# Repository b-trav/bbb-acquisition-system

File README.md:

# BEAGLEBONE BLACK ACQUISITION SYSTEM

__IMPORTANT: This project was last updated in 2017, so many commands and links are likely to be out of date.__

## Introduction

This project will show you how to create an 8 channel 24-bit 130 kSPS 
data acquisition system using a Beaglebone Black, four ADS1271 
Evaluation modules and a few other electronic bits and pieces.

The aim of this project is to give people access to a reliable, 
high-precision data acquisition system which runs at a respectable 
sample rate without having to shell out tens of thousands of dollars.

## Client-side App

The acquisition system can be controlled with any browser, however, to check on the
progress of a recording, or look at the third octave levels of an input, it is necessary
to run a python script on the computer used to access the BBBAS.

To use the client-side app, you need to install python, as well as numpy and bokeh.
So far, the client-side app has only been tested in linux.
The client side app is run using the command
```
BBBASDIR=~/bbb-acquisition-system
bokeh serve --unused-session-lifetime 10 --port 5006 $BBBASDIR/source/third_octave_local.py $BBBASDIR/source/record_progress.py
``` 
This assumes that you have cloned the bbb-acquisition-system repository into
your home directory.

## Bill of Materials

| Product | (Approx.) Price<sup>1</sup> (US$) |
|---------|----------------------------------:|
| [Beaglebone Black]                                          |  $55 |
| [ADS1271EVM] ( 4 @ $49 )                                    | $196 |
| [12V 2A DC Power Supply]<sup>2</sup>                        |   $4 |
| [2Gb microSD card]<sup>3</sup>                              |   $2 |
| [larger microSD card]<sup>4</sup>                           |   $4 |
| [BBB_ADS1271 Cape](#Cape)                                   |  $80 |
| [BBB ADS1271 Front Panel](#FrontPanel)                      |  $30 |
| [Wifi dongle] (optional)                                    |  $12 |
| __Case (optional)__ 
| [Base](#Base) (27 cm<sup>3</sup> of plastic)                |  $10 |
| [Cover](#Cover) (91 cm<sup>3</sup> of plastic)              |  $25 |
| __TOTAL__                                               | __$418__ |

[Beaglebone Black]:http://beagleboard.org/BLACK
[ADS1271EVM]: http://www.ti.com/tool/ads1271evm
[12V 2A DC Power Supply]: http://www.ebay.com/sch/12v+2a+power+supply
[2Gb microSD card]: http://www.ebay.com/sch/2Gb+micro+SD+card
[larger microSD card]: http://www.ebay.com/sch/micro+SD+card
[Wifi dongle]: https://www.adafruit.com/products/814
__Footnotes__:
 
<sup>1</sup>Some components will need to be purchased in quantities 
greater than those required by a single acquisition system, leading to 
a larger over-all cost for the creation of a single unit.

<sup>2</sup>The device will run with any supply voltage between 10 and 
20 volts.

<sup>3</sup>For storing the Linux Debian operating system flasher 
(Can be larger than 2Gb).

<sup>4</sup>For storing the acquired data.

## Software installation procedure

* Download the following compressed flasher image of the debian operating system 
  for the beaglebone black. 
  * [kernel: 3.8.13-bone79 Debian Wheezy image](https://rcn-ee.com/rootfs/bb.org/release/2015-11-03/console/BBB-eMMC-flasher-debian-7.9-console-armhf-2015-11-03-2gb.img.xz)

  > ### Background
  > 
  > There are a heap of different kernel versions of debian available 
  > to download,
  > thanks to the good work of [RobertCNelson](https://github.com/RobertCNelson).
  > These images can be found on the [Embedded Linux Wiki](http://elinux.org/Beagleboard:BeagleBoneBlack_Debian).
  > 
  > I am far from an expert in the world of linux or embedded systems, 
  > but as I understand it, there are two main distinctions with the 
  > kernels.
  > There are kernels 8.13.x which have good support for the 
  > capemanager, but are now rather old, and
  > then there are newer kernels which have better reliability with 
  > regard to wifi etc, but do not *yet* provide good support for adding 
  > capes or using the PRUs.
  > 
  > I have attempted to create an ADS1271 cape which works with 
  > newer kernels, but I have run into some issues. If you are adventurous,
  > you can try:
  > * [kernel: 4.1.16-ti-rt-r44 Debian Jessie image](https://rcn-ee.com/rootfs/bb.org/testing/2016-01-31/console/BBB-eMMC-flasher-debian-8.3-console-armhf-2016-01-31-2gb.img.xz)
  > 
  > CURRENT BUGS: 
  >   * Boot freezes for several minutes when wifi dongle is attached
  >   * Boot freezes for several minutes when PRU is enabled

* Copy this image onto a 2Gb microSD card (this is the minimum size – a 
  larger microSD card will work fine)

  * **Linux** :
  Follow [these instructions](http://www.ev3dev.org/docs/tutorials/writing-sd-card-image-linux-command-line/)

  * **Windows** :
  Follow [these instructions](https://learn.adafruit.com/beaglebone-black-installing-operating-systems/windows)

  * **Mac** :
  Follow [these instructions](https://learn.adafruit.com/beaglebone-black-installing-operating-systems/mac-os-x)

* Eject and insert the SD card into the BBB and power it up (you may need to hold down the SD card
  button on the BBB). 
  Wait for the image to be flashed to the emmc (takes a few minutes) while it is processing, the blues leds should be sweeping back and forth. On conclusion all the blue leds should be on (or wait another minute or so and the device should have powered itself down). 

* Remove the microSD card from the BBB, and save it in case you need to start the installation procedure again, or create another device. 

* **IMPORTANT!!!** LABEL the microSD card CLEARLY, as inserting this into a BBB and powering the device will wipe the eMMC on the beaglebone black.

* Insert a blank (fat32 formatted) microSD card into the BBB. 

* Power up the BBB by connecting the BBB to a computer via mini-USB. 

* WAIT a few minutes or so (be patient). NB: Probably best not to have the wifi
  dongle plugged in at this point.

* You should be able to connect to your beaglebone black.

* In order to connect to the beaglebone and get internet access, you need to do the following
on your computer:

  * **Linux** :
  
	Open a terminal, and type:

  ```
  sudo su
  ifconfig -a
  # Find out which connection the BBB is on (generally eth3, eth4, etc)
  # and which connection your internet is using (generally wlan0 etc)
  # in this example, the BBB is on eth5 and my internet is on wlan0
  ifconfig eth5 192.168.7.1
  iptables --table nat --append POSTROUTING --out-interface wlan0 -j MASQUERADE
  iptables --append FORWARD --in-interface eth5 -j ACCEPT
  echo 1 > /proc/sys/net/ipv4/ip_forward
  exit
  ssh debian@192.168.7.2
  ```

  * **Windows** : 
   
	Follow [these instructions](https://learn.adafruit.com/ssh-to-beaglebone-black-over-usb/installing-drivers-windows), and then [these instructions](https://learn.adafruit.com/ssh-to-beaglebone-black-over-usb/ssh-with-windows-and-putty).

  * **Mac** : 
   
	Follow [these instructions](https://learn.adafruit.com/ssh-to-beaglebone-black-over-usb/installing-drivers-mac), and then open a terminal and type:
  
  ```
  ssh debian@192.168.7.2
  ```

* Once you have ssh access to the beaglebone, log in via ssh (the default password is temppwd) and then type:

  ```
  sudo ip route add default via 192.168.7.1
  sudo sh -c "echo 'nameserver 8.8.8.8' >> /etc/resolv.conf"
  sudo apt-get -y update
  sudo apt-get -y install git locales
  sudo dpkg-reconfigure locales
  sudo dpkg-reconfigure tzdata
  sudo sh -c "locale > /etc/locale.conf"
  git clone https://github.com/bbb-acquisition-system
  sudo bbb-acquisition-system/install.sh  2>&1 | tee install-bbb-as-log.txt
  ```
  
  Unfortunately this installation procedure takes a reasonably long time 
  (depending on your internet access speed) 
  because we need to install quite a few applications.
  The main hold-up is a couple of python packages (numpy and jupyter),
  which take roughly 35 minutes and 15 minutes respectively to install.
  This gives a total install time of around an hour. 
  Assuming you've set up your locale and timezone, the only user inputs
  are a root password, and then some wifi info at the very end. 
  So after giving your root password,
  go take a long walk, and come back in around an hour.

* After re-booting the BBB you should be able to access your 
  Beaglebone Black Acquisition System by going
  to the ip address of the BBB using a browser of your choice. 

## Building the boards

The BBB Acquisition System requires two printed computer boards (PCBs) to function correctly.
The [Eagle](http://www.cadsoftusa.com/download-eagle/) schematics and 
boards are contained in the PCBs directory, this directory also contains
a set of gerber files for each board.
These boards can be produced using the PCB production company of your choice, or can be generated
in-house, assuming you have the relevant know-how.

### BBB ADS1271 Cape

This board provides power, a real-time clock and the connections between the BBB and
the ADS1271EVMs. 
[Here](PCBs/BBB_ADS1271_cape_parts.html) is a parts list for this board.
Some of the items can only be purchased in large quantities, such as the surface mounted LEDs.
These are not strictly necessary, so if you do not have access to some surface mounted LEDs,
then these can be omitted.

### BBB ADS1271 Front Panel

This board provides the inputs to the system as well as on/off and recording lights and buttons.
[Here](PCBs/BBB_ADS1271_front_panel_parts.html) is a parts list for this board.

## Building the case

The case for the unit is optional, although highly recommended.
The case directory contains the [blender](https://www.blender.org/) 
and [stl](https://en.wikipedia.org/wiki/STL_%28file_format%29) files for the case.
Once again, if you have access to a 3D printer, you can produce this yourself, otherwise
there are plenty of [3D printing companies](http://3dprintingpricecheck.com/) that you could use.

### Base

### Cover

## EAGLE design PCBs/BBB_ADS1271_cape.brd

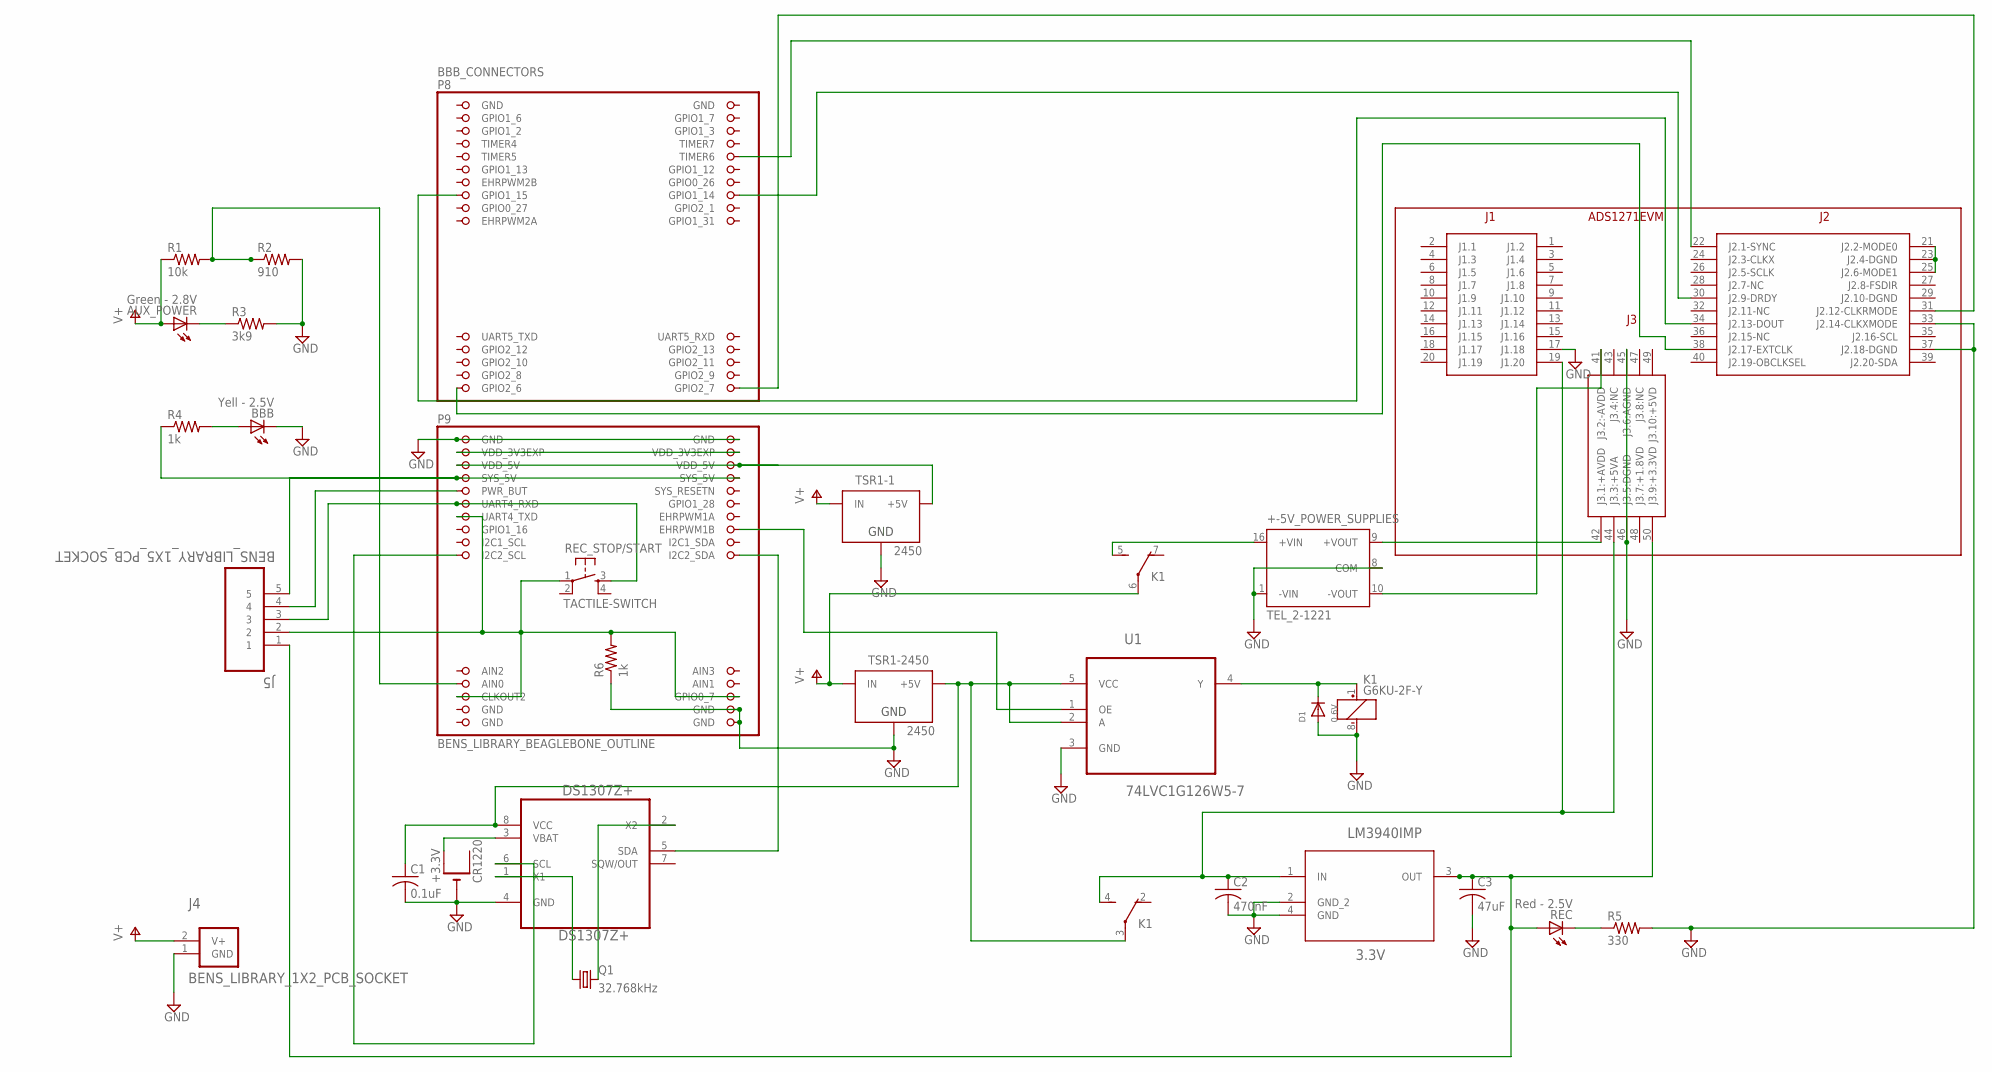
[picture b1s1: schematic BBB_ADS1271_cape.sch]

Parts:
+-5V_POWER_SUPPLIES: TEL_2-1221; TRACOPOWER2W
ADS1271_CONNECTORS: BENS_LIBRARY_ADS1271EVM
AUX_POWER: Green - 2.8V; CHIPLED_0805
BBB: Yell - 2.5V; CHIPLED_0805
BBB_CONNECTORS: BENS_LIBRARY_BEAGLEBONE_OUTLINE; BENS_LIBRARY_BEAGLEBONE_SHIELD
C1: 0.1uF; C0805K
C2: 470nF; C0805K
C3: 47uF; C0805K
CR1220: +3.3V; ADAFRUIT_CR1220-SMD
D1: 0.6V; SOD-123FL
DS1307Z+: DS1307Z+; MAXIM_BY_ELEMENT14_BATCH_1_SOIC127P600X175-8N
J4: BENS_LIBRARY_1X2_PCB_SOCKET
J5: BENS_LIBRARY_1X5_PCB_SOCKET; BENS_LIBRARY_SAMTEC_SSM-15-L-DV-BE
K1: G6KU-2F-Y
LM3940IMP: 3.3V; NSC_BY_ELEMENT14_BATCH_1.1_SOT230P696X180-4N
Q1: 32.768kHz; TC38H
R1: 10k; ADAFRUIT_R0805
R2: 910; ADAFRUIT_R0805
R3: 3k9; ADAFRUIT_R0805
R4, R6: 1k; ADAFRUIT_R0805
R5: 330; ADAFRUIT_R0805
REC: Red - 2.5V; CHIPLED_0805
REC_STOP/START: TACTILE-SWITCH; 7914G-6MM
TSR1-1, TSR1-2450: 2450; STEELCAVEROBOTICS-POWER_TSR-1
U1: 74LVC1G126W5-7; SOT95P280X145-5N

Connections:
3.3V_BBB_1: BBB_CONNECTORS.57 (UART4_RXD), J5.3, REC_STOP/START.3
3.3V_BBB_2: ADS1271_CONNECTORS.31 (J2.12-CLKRMODE), BBB_CONNECTORS.46 (GPIO2_7)
3.3V_RELAY: ADS1271_CONNECTORS.50 (J3.9:+3.3VD), C3.1, J5.1, LM3940IMP.3 (OUT), REC.A
5V: C1.1, DS1307Z+.8 (VCC), K1.3, TSR1-2450.3 (+5V), U1.2 (A), U1.5 (VCC)
5V_BBB: BBB_CONNECTORS.51 (VDD_5V), BBB_CONNECTORS.52 (VDD_5V), TSR1-1.3 (+5V)
5V_RELAY: ADS1271_CONNECTORS.19 (J1.20), ADS1271_CONNECTORS.44 (J3.3:+5VA), C2.1, K1.4 (S), LM3940IMP.1 (IN)
+5V_OP_AMP: +-5V_POWER_SUPPLIES.9 (+VOUT), ADS1271_CONNECTORS.42 (J3.1:+AVDD)
-5V_OP_AMP: +-5V_POWER_SUPPLIES.10 (-VOUT), ADS1271_CONNECTORS.41 (J3.2:-AVDD)
CLK: ADS1271_CONNECTORS.38 (J2.17-EXTCLK), BBB_CONNECTORS.45 (GPIO2_6)
DGND: ADS1271_CONNECTORS.21 (J2.2-MODE0), ADS1271_CONNECTORS.23 (J2.4-DGND), ADS1271_CONNECTORS.25 (J2.6-MODE1)
DOUT: ADS1271_CONNECTORS.34 (J2.13-DOUT), BBB_CONNECTORS.15 (GPIO1_15)
DRDY: ADS1271_CONNECTORS.30 (J2.9-DRDY), BBB_CONNECTORS.16 (GPIO1_14)
GND: +-5V_POWER_SUPPLIES.1 (-VIN), +-5V_POWER_SUPPLIES.8 (COM), ADS1271_CONNECTORS.17 (J1.18), ADS1271_CONNECTORS.33 (J2.14-CLKXMODE), ADS1271_CONNECTORS.37 (J2.18-DGND), ADS1271_CONNECTORS.45 (J3.6:AGND), ADS1271_CONNECTORS.46 (J3.5:DGND), BBB.C, BBB_CONNECTORS.47 (GND), BBB_CONNECTORS.48 (GND), BBB_CONNECTORS.89 (GND), BBB_CONNECTORS.90 (GND), BBB_CONNECTORS.91 (GND), BBB_CONNECTORS.92 (GND), C1.2, C2.2, C3.2, CR1220.-, D1.A, DS1307Z+.4 (GND), J4.1 (GND), K1.8 (-), LM3940IMP.2 (GND_2), LM3940IMP.4 (GND), R2.2, R3.2, R5.2, R6.1, TSR1-1.2 (GND), TSR1-2450.2 (GND), U1.3 (GND)
unnamed: CR1220.+$2 (+1), DS1307Z+.3 (VBAT)
unnamed: +-5V_POWER_SUPPLIES.16 (+VIN), K1.5 (S)
unnamed: BBB_CONNECTORS.85 (AIN0), R1.2, R2.1
unnamed: BBB_CONNECTORS.66 (I2C2_SDA), DS1307Z+.5 (SDA)
unnamed: BBB_CONNECTORS.65 (I2C2_SCL), DS1307Z+.6 (SCL)
unnamed: DS1307Z+.2 (X2), Q1.2
unnamed: DS1307Z+.1 (X1), Q1.1
unnamed: AUX_POWER.C, R3.1
unnamed: D1.C, K1.1 (+), U1.4 (Y)
unnamed: R5.1, REC.C
unnamed: BBB.A, R4.2
P8.9: BBB_CONNECTORS.62 (EHRPWM1B), U1.1 (OE)
PWR_BUT: BBB_CONNECTORS.55 (PWR_BUT), J5.4
REC_SWITCH: BBB_CONNECTORS.59 (UART4_TXD), BBB_CONNECTORS.87 (CLKOUT2), BBB_CONNECTORS.88 (GPIO0_7), J5.2, R6.2, REC_STOP/START.1
SYNC: ADS1271_CONNECTORS.22 (J2.1-SYNC), BBB_CONNECTORS.10 (TIMER6)
SYS_5V: BBB_CONNECTORS.53 (SYS_5V), BBB_CONNECTORS.54 (SYS_5V), J5.5, R4.1
V+: AUX_POWER.A, J4.2 (V+), K1.6, R1.1, TSR1-1.1 (IN), TSR1-2450.1 (IN)
VDD_3V3EXP: BBB_CONNECTORS.49 (VDD_3V3EXP), BBB_CONNECTORS.50 (VDD_3V3EXP)

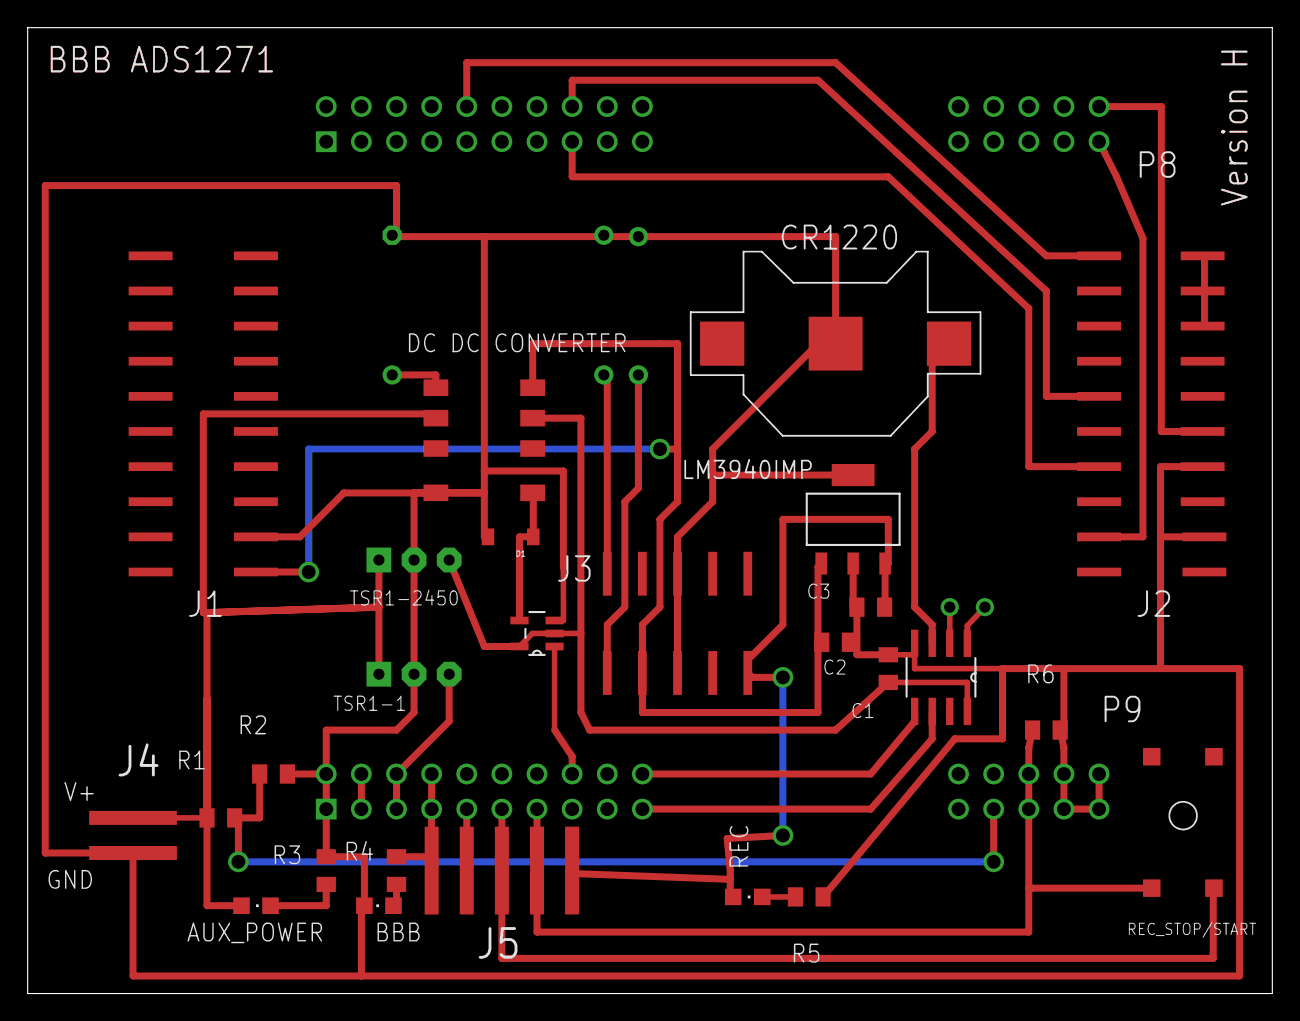
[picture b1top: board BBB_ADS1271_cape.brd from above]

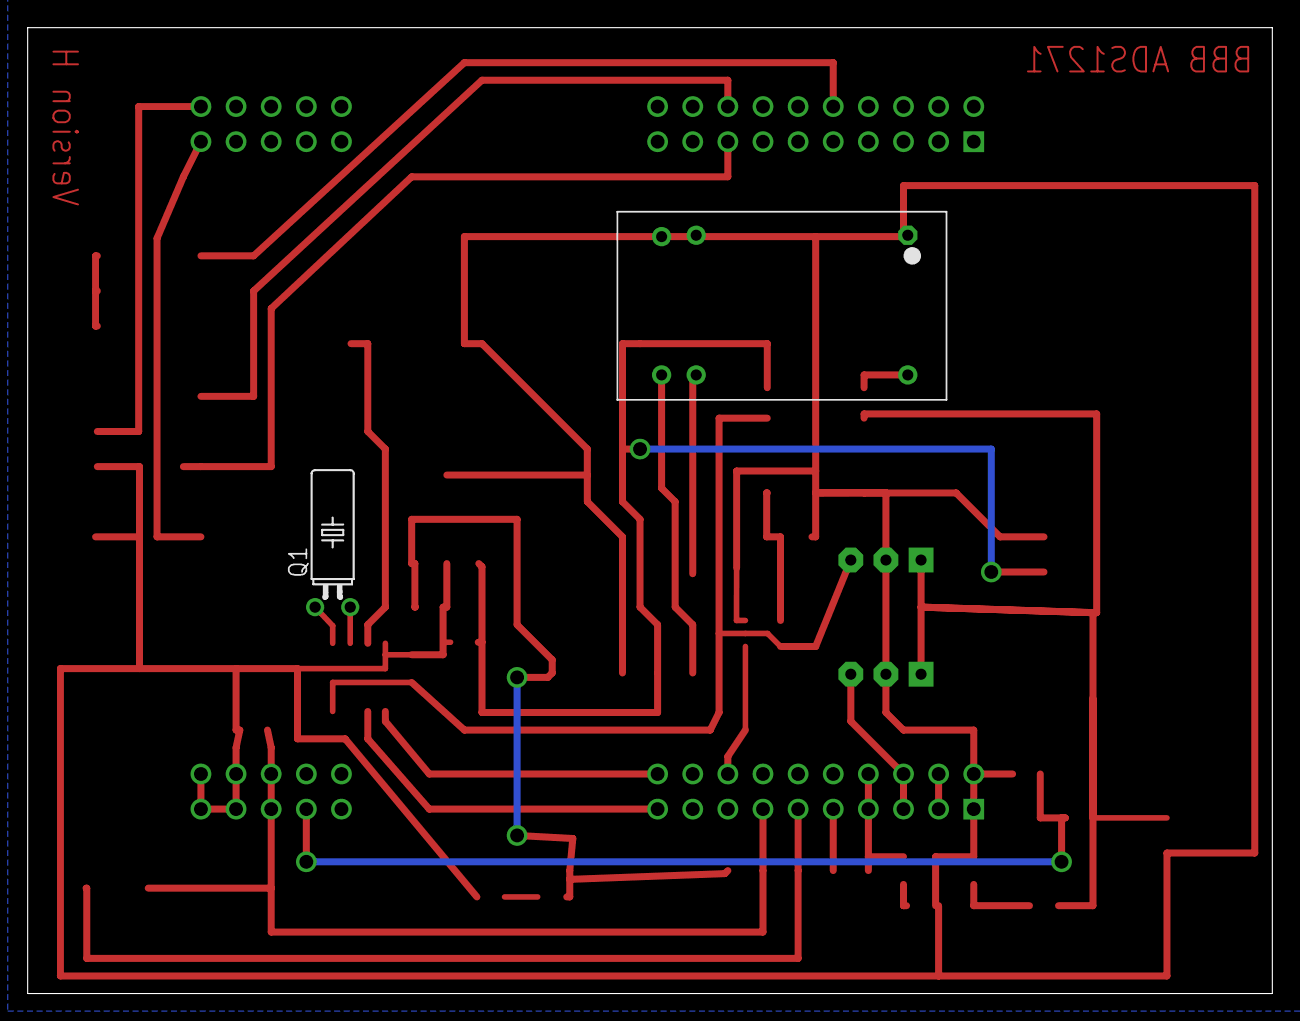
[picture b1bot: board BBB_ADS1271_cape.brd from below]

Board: 2 copper layers, 90.0 x 69.8 mm, 27 parts (4 on the bottom side), 31 nets.

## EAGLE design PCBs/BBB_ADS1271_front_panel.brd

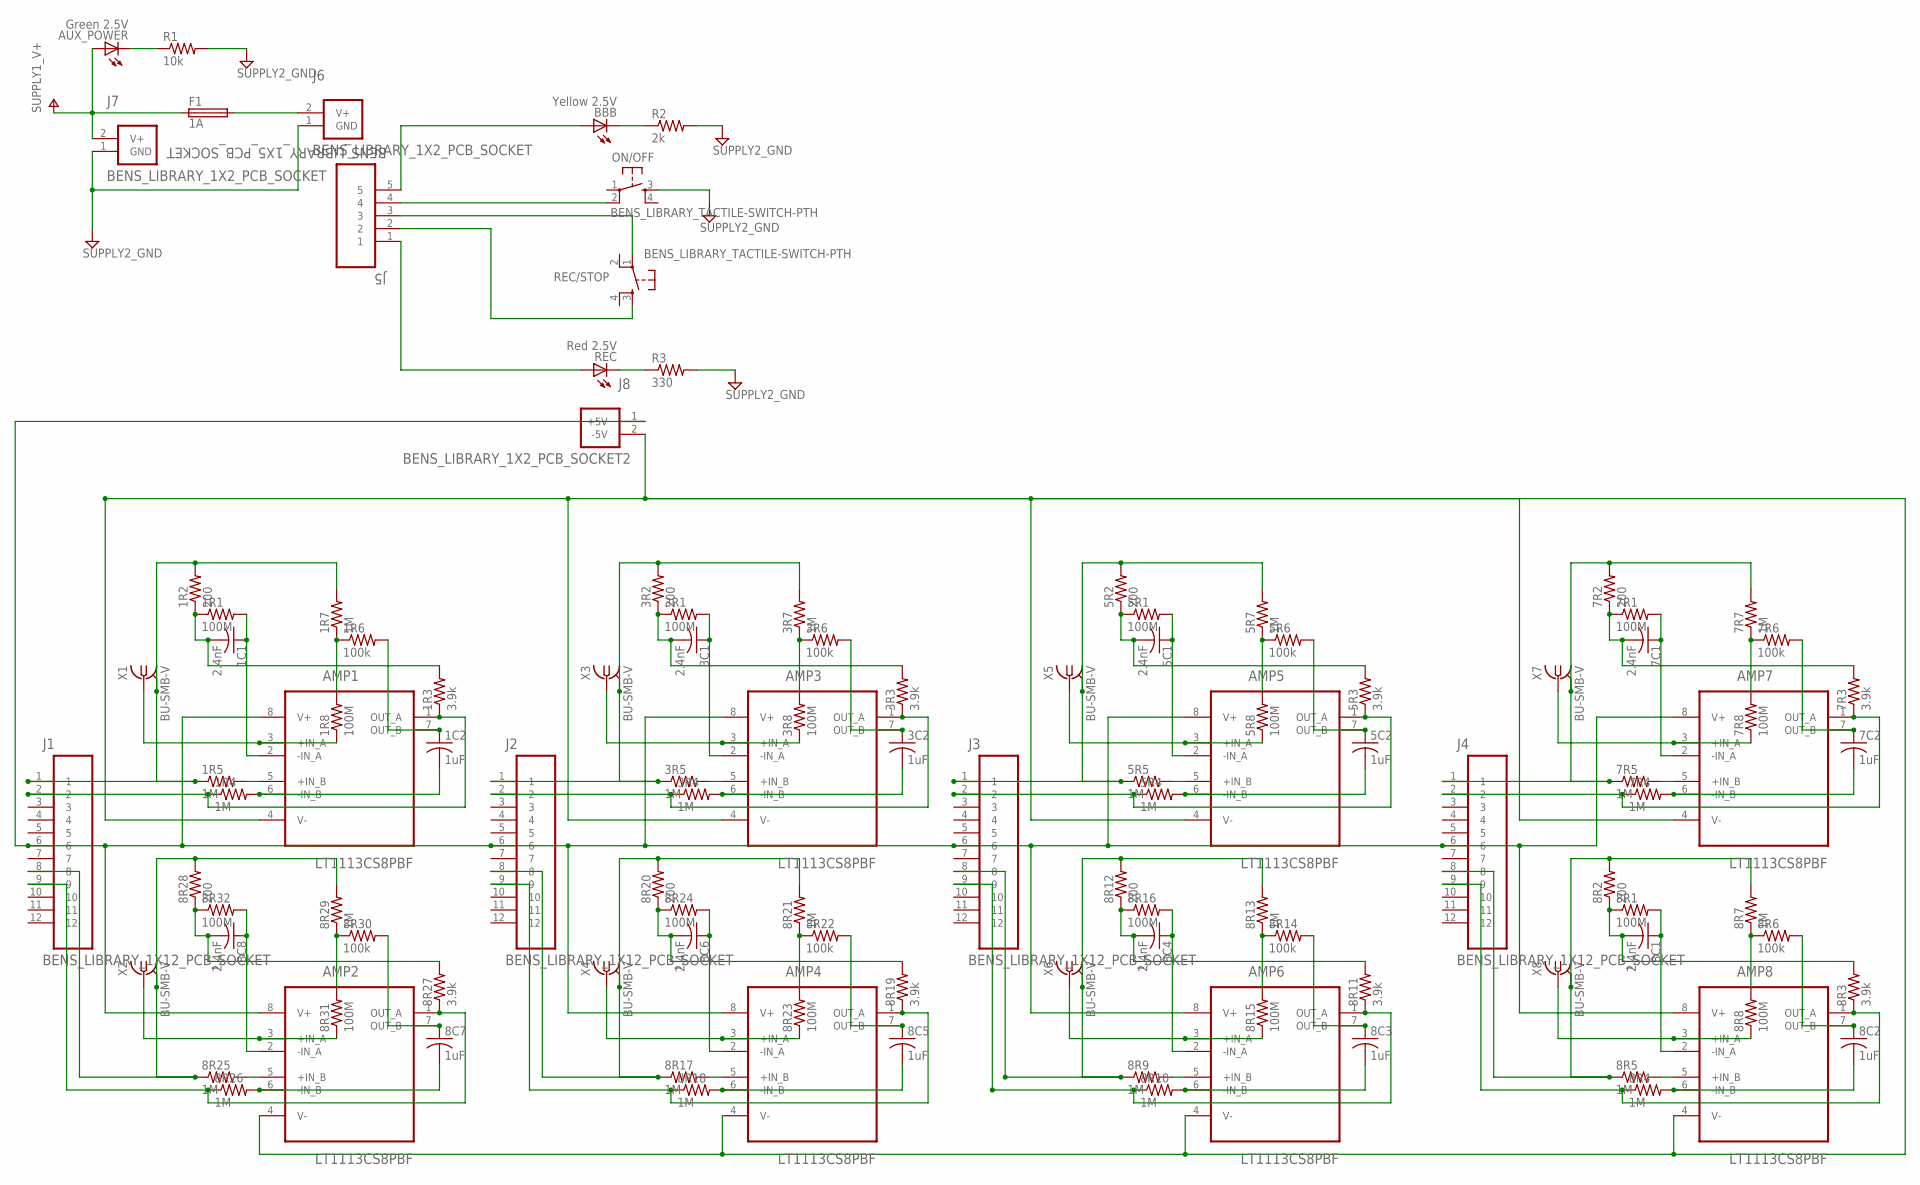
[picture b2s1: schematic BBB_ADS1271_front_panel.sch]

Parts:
1C1, 3C1, 5C1, 7C1, 8C1, 8C4, 8C6, 8C8: 2.4nF; ADAFRUIT_C0805K
1C2, 3C2, 5C2, 7C2, 8C2, 8C3, 8C5, 8C7: 1uF; ADAFRUIT_C0805K
1R1, 1R8, 3R1, 3R8, 5R1, 5R8, 7R1, 7R8, 8R1, 8R8, 8R15, 8R16, 8R23, 8R24, 8R31, 8R32: 100M; ADAFRUIT_R0805
1R2, 3R2, 5R2, 7R2, 8R2, 8R12, 8R20, 8R28: 200; ADAFRUIT_R0805
1R3, 3R3, 5R3, 7R3, 8R3, 8R11, 8R19, 8R27: 3.9k; ADAFRUIT_R0805
1R4, 1R5, 1R7, 3R4, 3R5, 3R7, 5R4, 5R5, 5R7, 7R4, 7R5, 7R7, 8R4, 8R5, 8R7, 8R9, 8R10, 8R13, 8R17, 8R18, 8R21, 8R25, 8R26, 8R29: 1M; ADAFRUIT_R0805
1R6, 3R6, 5R6, 7R6, 8R6, 8R14, 8R22, 8R30: 100k; ADAFRUIT_R0805
AMP1, AMP2, AMP3, AMP4, AMP5, AMP6, AMP7, AMP8: LT1113CS8PBF; SOIC127P600X175-8N
AUX_POWER: Green 2.5V; ADAFRUIT_LED5MM
BBB: Yellow 2.5V; ADAFRUIT_LED5MM
F1: 1A; LITTLEFUSE_PACKAGE
J1, J2, J3, J4: BENS_LIBRARY_1X12_PCB_SOCKET; BENS_LIBRARY_SAMTEC_SSM-112-L-DV-BE
J5: BENS_LIBRARY_1X5_PCB_SOCKET; BENS_LIBRARY_SAMTEC_SSM-15-L-DV-BE
J6, J7: BENS_LIBRARY_1X2_PCB_SOCKET
J8: BENS_LIBRARY_1X2_PCB_SOCKET2
ON/OFF: BENS_LIBRARY_TACTILE-SWITCH-PTH; BENS_LIBRARY_TAC-SWITCH-PTH
R1: 10k; ADAFRUIT_R0805
R2: 2k; ADAFRUIT_R0805
R3: 330; ADAFRUIT_R0805
REC: Red 2.5V; ADAFRUIT_LED5MM
REC/STOP: BENS_LIBRARY_TACTILE-SWITCH-PTH; BENS_LIBRARY_TAC-SWITCH-PTH
X1, X2, X3, X4, X5, X6, X7, X8: BU-SMB-V

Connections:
1+IN_B: 1R5.2, AMP1.5 (+IN_B)
1-IN_A: 1C1.1, 1R1.2, AMP1.2 (-IN_A)
1-IN_B: 1C2.2, 1R4.2, AMP1.6 (-IN_B)
1OUT_B: 1C2.1, 1R6.2, AMP1.7 (OUT_B)
1W1: 1C1.2, 1R1.1, 1R2.1, 1R3.2
1W2: 1R6.1, 1R7.1, 1R8.2
2+IN_B: 8R25.2, AMP2.5 (+IN_B)
2-IN_A: 8C8.1, 8R32.2, AMP2.2 (-IN_A)
2-IN_B: 8C7.2, 8R26.2, AMP2.6 (-IN_B)
2OUT_B: 8C7.1, 8R30.2, AMP2.7 (OUT_B)
2W1: 8C8.2, 8R27.2, 8R28.1, 8R32.1
2W2: 8R29.1, 8R30.1, 8R31.2
3+IN_B: 3R5.2, AMP3.5 (+IN_B)
3-IN_A: 3C1.1, 3R1.2, AMP3.2 (-IN_A)
3-IN_B: 3C2.2, 3R4.2, AMP3.6 (-IN_B)
3OUT_B: 3C2.1, 3R6.2, AMP3.7 (OUT_B)
3W1: 3C1.2, 3R1.1, 3R2.1, 3R3.2
3W2: 3R6.1, 3R7.1, 3R8.2
4+IN_B: 8R17.2, AMP4.5 (+IN_B)
4-IN_A: 8C6.1, 8R24.2, AMP4.2 (-IN_A)
4-IN_B: 8C5.2, 8R18.2, AMP4.6 (-IN_B)
4OUT_B: 8C5.1, 8R22.2, AMP4.7 (OUT_B)
4W1: 8C6.2, 8R19.2, 8R20.1, 8R24.1
4W2: 8R21.1, 8R22.1, 8R23.2
5+IN_B: 5R5.2, AMP5.5 (+IN_B)
5-IN_A: 5C1.1, 5R1.2, AMP5.2 (-IN_A)
5-IN_B: 5C2.2, 5R4.2, AMP5.6 (-IN_B)
5OUT_B: 5C2.1, 5R6.2, AMP5.7 (OUT_B)
5W1: 5C1.2, 5R1.1, 5R2.1, 5R3.2
5W2: 5R6.1, 5R7.1, 5R8.2
6+IN_B: 8R9.2, AMP6.5 (+IN_B)
6-IN_A: 8C4.1, 8R16.2, AMP6.2 (-IN_A)
6-IN_B: 8C3.2, 8R10.2, AMP6.6 (-IN_B)
6OUT_B: 8C3.1, 8R14.2, AMP6.7 (OUT_B)
6W1: 8C4.2, 8R11.2, 8R12.1, 8R16.1
6W2: 8R13.1, 8R14.1, 8R15.2
7+IN_B: 7R5.2, AMP7.5 (+IN_B)
7-IN_A: 7C1.1, 7R1.2, AMP7.2 (-IN_A)
7-IN_B: 7C2.2, 7R4.2, AMP7.6 (-IN_B)
7OUT_B: 7C2.1, 7R6.2, AMP7.7 (OUT_B)
7W1: 7C1.2, 7R1.1, 7R2.1, 7R3.2
7W2: 7R6.1, 7R7.1, 7R8.2
8+IN_B: 8R5.2, AMP8.5 (+IN_B)
8-IN_A: 8C1.1, 8R1.2, AMP8.2 (-IN_A)
8-IN_B: 8C2.2, 8R4.2, AMP8.6 (-IN_B)
8OUT_B: 8C2.1, 8R6.2, AMP8.7 (OUT_B)
8W1: 8C1.2, 8R1.1, 8R2.1, 8R3.2
8W2: 8R6.1, 8R7.1, 8R8.2
+5V: AMP1.8 (V+), AMP2.8 (V+), AMP3.8 (V+), AMP4.8 (V+), AMP5.8 (V+), AMP6.8 (V+), AMP7.8 (V+), AMP8.8 (V+), J1.6, J2.6, J3.6, J4.6, J8.1 (+5V)
-5V: AMP1.4 (V-), AMP2.4 (V-), AMP3.4 (V-), AMP4.4 (V-), AMP5.4 (V-), AMP6.4 (V-), AMP7.4 (V-), AMP8.4 (V-), J8.2 (-5V)
ADC1_NEG: 1R3.1, 1R4.1, AMP1.1 (OUT_A), J1.2
ADC1_POS: 1R2.2, 1R5.1, 1R7.2, J1.1, X1.2, X1.3 (2), X1.4 (2), X1.5 (2)
ADC2_NEG: 8R26.1, 8R27.1, AMP2.1 (OUT_A), J1.9
ADC2_POS: 8R25.1, 8R28.2, 8R29.2, J1.8, X2.2, X2.3 (2), X2.4 (2), X2.5 (2)
ADC3_NEG: 3R3.1, 3R4.1, AMP3.1 (OUT_A), J2.2
ADC3_POS: 3R2.2, 3R5.1, 3R7.2, J2.1, X3.2, X3.3 (2), X3.4 (2), X3.5 (2)
ADC4_NEG: 8R18.1, 8R19.1, AMP4.1 (OUT_A), J2.9
ADC4_POS: 8R17.1, 8R20.2, 8R21.2, J2.8, X4.2, X4.3 (2), X4.4 (2), X4.5 (2)
ADC5_NEG: 5R3.1, 5R4.1, AMP5.1 (OUT_A), J3.2
ADC5_POS: 5R2.2, 5R5.1, 5R7.2, J3.1, X5.2, X5.3 (2), X5.4 (2), X5.5 (2)
ADC6_NEG: 8R10.1, 8R11.1, AMP6.1 (OUT_A), J3.9
ADC6_POS: 8R9.1, 8R12.2, 8R13.2, J3.8, X6.2, X6.3 (2), X6.4 (2), X6.5 (2)
ADC7_NEG: 7R3.1, 7R4.1, AMP7.1 (OUT_A), J4.2
ADC7_POS: 7R2.2, 7R5.1, 7R7.2, J4.1, X7.2, X7.3 (2), X7.4 (2), X7.5 (2)
ADC8_NEG: 8R3.1, 8R4.1, AMP8.1 (OUT_A), J4.9
ADC8_POS: 8R2.2, 8R5.1, 8R7.2, J4.8, X8.2, X8.3 (2), X8.4 (2), X8.5 (2)
GND: J6.1 (GND), J7.1 (GND), ON/OFF.3, R1.2, R2.2, R3.2
INPUT1_NEG: 1R8.1, AMP1.3 (+IN_A), X1.1
INPUT2_NEG: 8R31.1, AMP2.3 (+IN_A), X2.1
INPUT3_NEG: 3R8.1, AMP3.3 (+IN_A), X3.1
INPUT4_NEG: 8R23.1, AMP4.3 (+IN_A), X4.1
INPUT5_NEG: 5R8.1, AMP5.3 (+IN_A), X5.1
INPUT6_NEG: 8R15.1, AMP6.3 (+IN_A), X6.1
INPUT7_NEG: 7R8.1, AMP7.3 (+IN_A), X7.1
INPUT8_NEG: 8R8.1, AMP8.3 (+IN_A), X8.1
unnamed: BBB.A, J5.5
unnamed: AUX_POWER.K (C), R1.1
unnamed: J5.1, REC.A
unnamed: J5.4, ON/OFF.2
unnamed: J5.3, REC/STOP.1
unnamed: J5.2, REC/STOP.3
unnamed: R3.1, REC.K (C)
unnamed: BBB.K (C), R2.1
V+: AUX_POWER.A, F1.P$1 (1), J7.2 (V+)
V+_FUSED: F1.P$2 (2), J6.2 (V+)

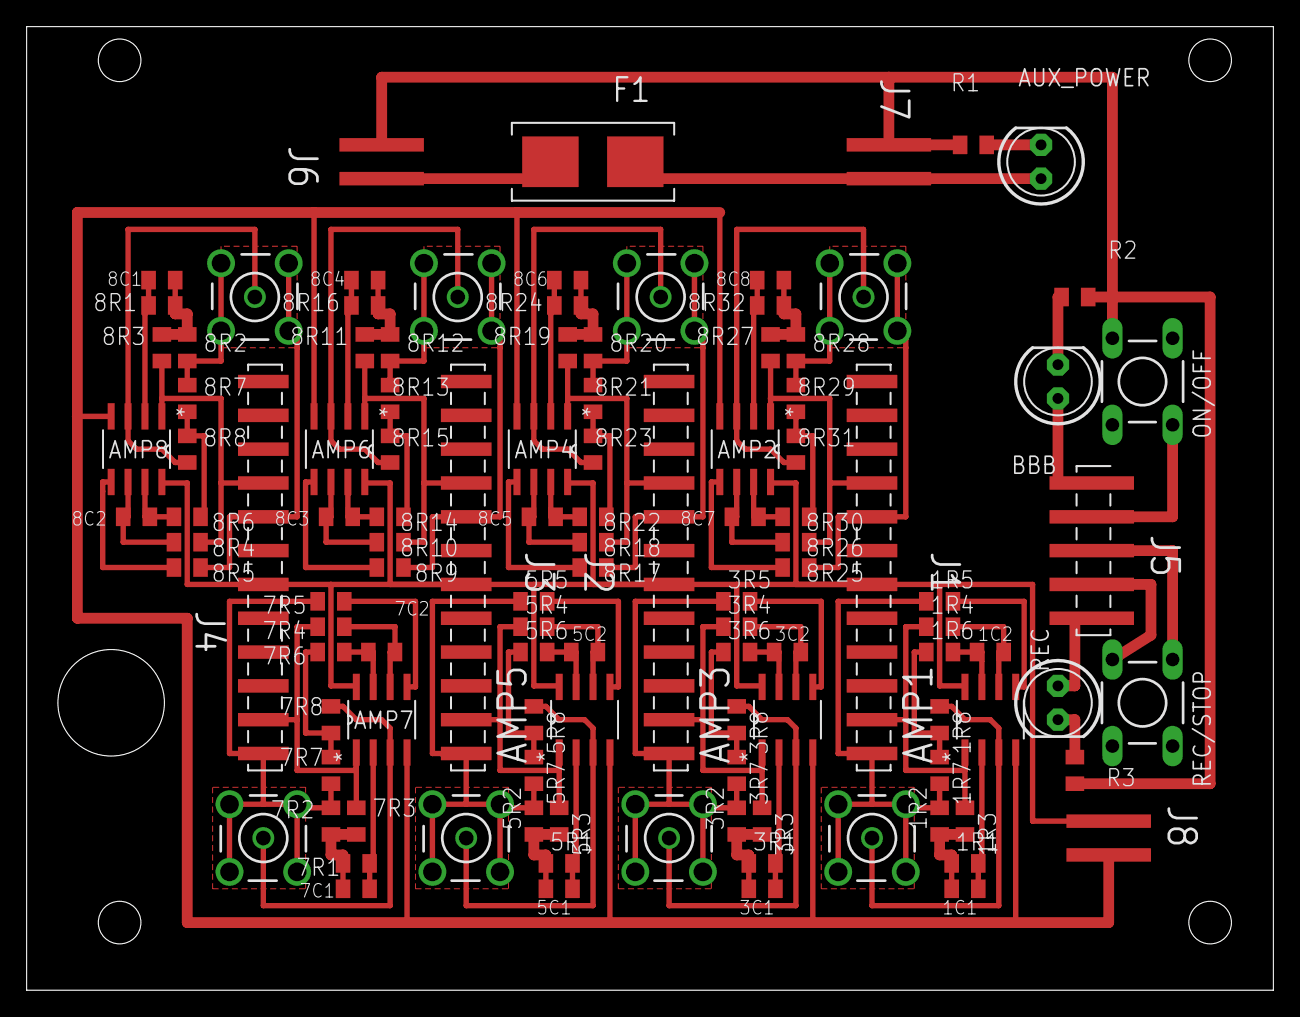
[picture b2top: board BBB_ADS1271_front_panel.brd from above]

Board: 2 copper layers, 93.7 x 72.4 mm, 113 parts (0 on the bottom side), 85 nets.

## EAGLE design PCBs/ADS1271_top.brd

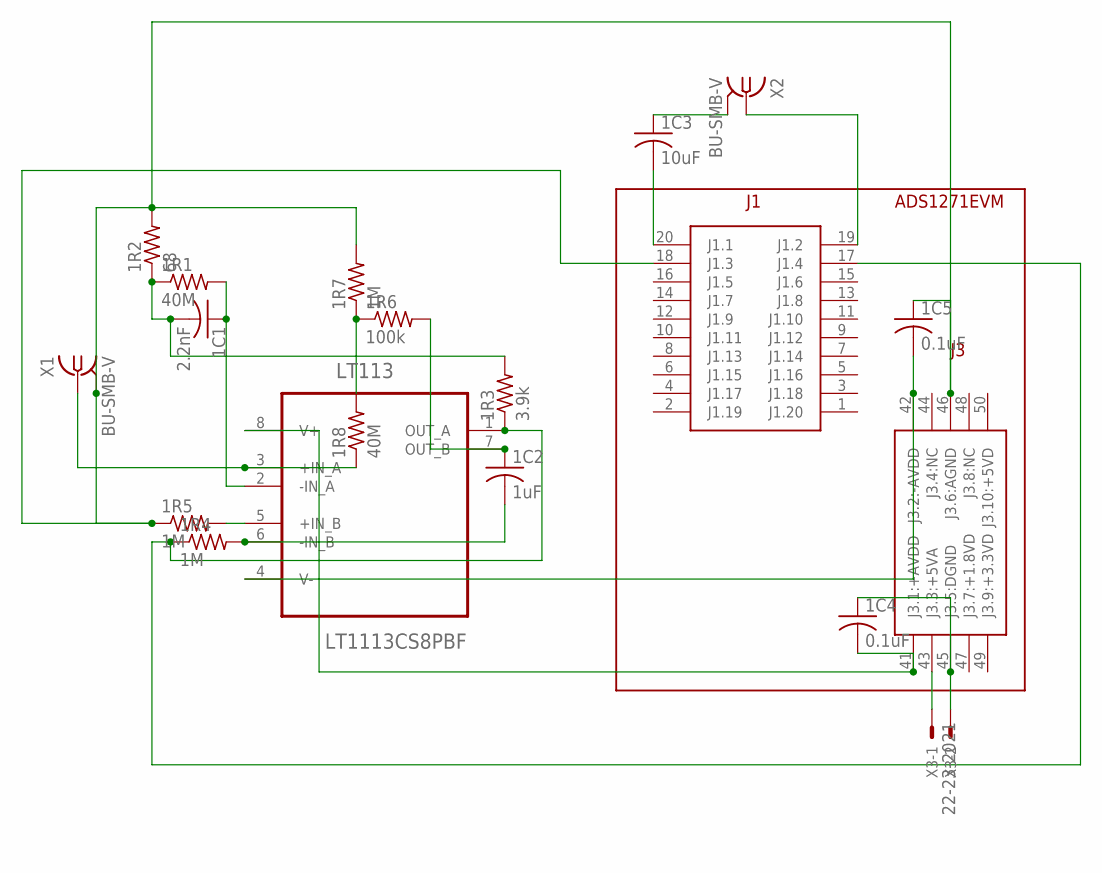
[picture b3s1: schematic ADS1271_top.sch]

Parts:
1C1: 2.2nF; ADAFRUIT_C0805K
1C2: 1uF; ADAFRUIT_C0805K
1C3: 10uF; ADAFRUIT_C0805K
1C4, 1C5: 0.1uF; ADAFRUIT_C0805K
1R1, 1R8: 40M; ADAFRUIT_R0805
1R2: 68; ADAFRUIT_R0805
1R3: 3.9k; ADAFRUIT_R0805
1R4, 1R5, 1R7: 1M; ADAFRUIT_R0805
1R6: 100k; ADAFRUIT_R0805
ADS1271_CONNECTORS: BENS_LIBRARY_ADS1271EVM_PART
LT113: LT1113CS8PBF; SOIC127P600X175-8N
X1, X2: BU-SMB-V
X3: 22-23-2021

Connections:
1+IN_B: 1R5.2, LT113.5 (+IN_B)
1-IN_A: 1C1.1, 1R1.2, LT113.2 (-IN_A)
1-IN_B: 1C2.2, 1R4.2, LT113.6 (-IN_B)
1OUT_B: 1C2.1, 1R6.2, LT113.7 (OUT_B)
1W1: 1C1.2, 1R1.1, 1R2.1, 1R3.2
1W2: 1R6.1, 1R7.1, 1R8.2
ADC1_NEG: 1R3.1, 1R4.1, ADS1271_CONNECTORS.17 (J1.4), LT113.1 (OUT_A)
ADC1_POS: 1C4.1, 1C5.1, 1R2.2, 1R5.1, 1R7.2, ADS1271_CONNECTORS.18 (J1.3), ADS1271_CONNECTORS.45 (J3.5:DGND), ADS1271_CONNECTORS.46 (J3.6:AGND), X1.2, X1.3 (2), X1.4 (2), X1.5 (2), X3.2
ADC2_GND: 1C3.1, X2.2, X2.3 (2), X2.4 (2), X2.5 (2)
ADC2_NEG: ADS1271_CONNECTORS.19 (J1.2), X2.1
ADC2_POS: 1C3.2, ADS1271_CONNECTORS.20 (J1.1)
INPUT1_NEG: 1R8.1, LT113.3 (+IN_A), X1.1
unnamed: ADS1271_CONNECTORS.43 (J3.3:+5VA), X3.1
unnamed: 1C5.2, ADS1271_CONNECTORS.42 (J3.2:-AVDD), LT113.4 (V-)
unnamed: 1C4.2, ADS1271_CONNECTORS.41 (J3.1:+AVDD), LT113.8 (V+)

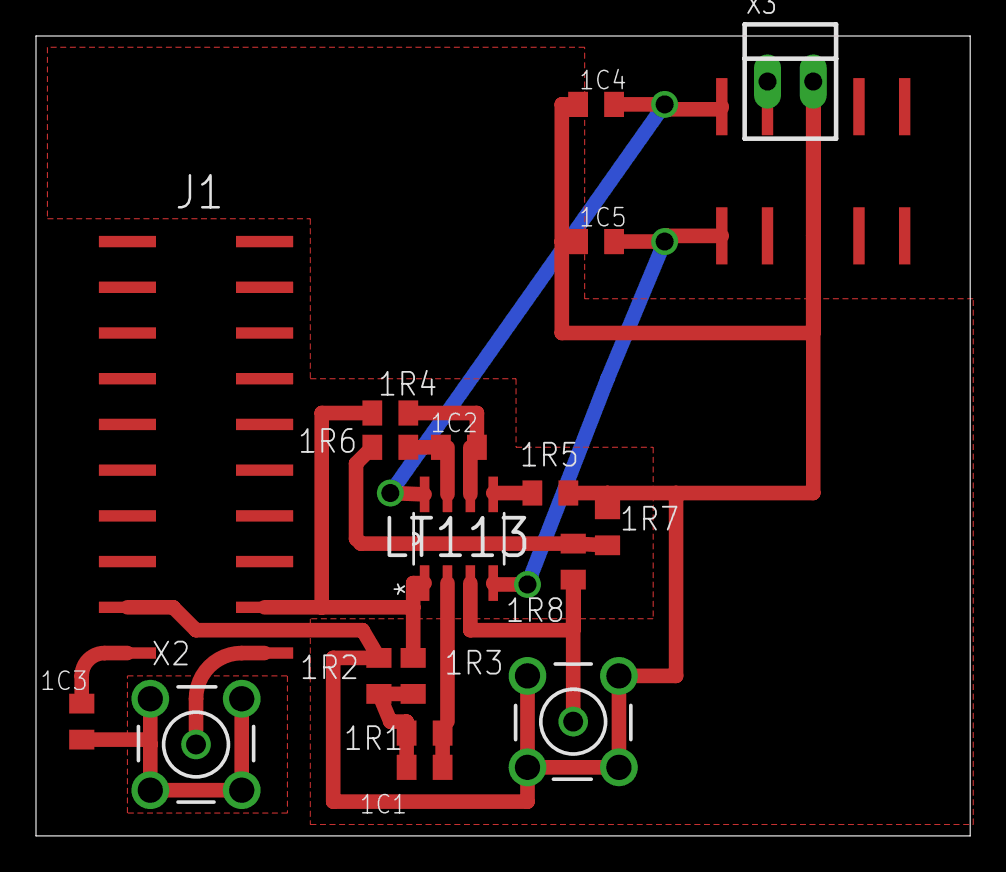
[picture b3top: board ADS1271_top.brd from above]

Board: 2 copper layers, 51.9 x 44.4 mm, 18 parts (0 on the bottom side), 15 nets.

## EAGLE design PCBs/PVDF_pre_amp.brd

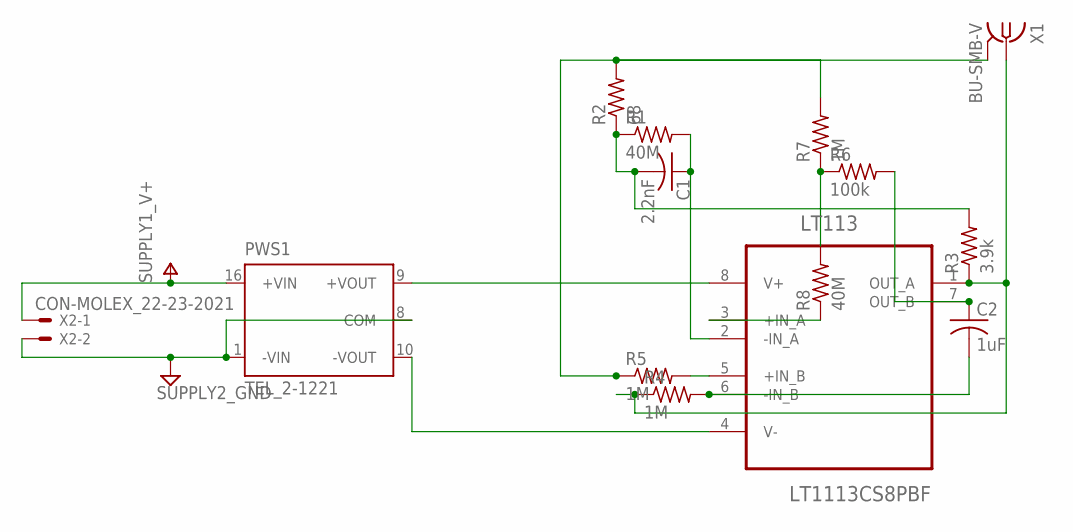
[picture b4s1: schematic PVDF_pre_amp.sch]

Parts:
C1: 2.2nF; ADAFRUIT_C0805K
C2: 1uF; ADAFRUIT_C0805K
LT113: LT1113CS8PBF; SOIC127P600X175-8N
PWS1: TEL_2-1221; TRACOPOWER2W
R1, R8: 40M; ADAFRUIT_R0805
R2: 68; ADAFRUIT_R0805
R3: 3.9k; ADAFRUIT_R0805
R4, R5, R7: 1M; ADAFRUIT_R0805
R6: 100k; ADAFRUIT_R0805
X1: BU-SMB-V
X2: CON-MOLEX_22-23-2021

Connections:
1+IN_B: LT113.5 (+IN_B), R5.2
1-IN_A: C1.1, LT113.2 (-IN_A), R1.2
1-IN_B: C2.2, LT113.6 (-IN_B), R4.2
1OUT_B: C2.1, LT113.7 (OUT_B), R6.2
1W1: C1.2, R1.1, R2.1, R3.2
1W2: R6.1, R7.1, R8.2
+AVDD: LT113.8 (V+), PWS1.9 (+VOUT)
-AVDD: LT113.4 (V-), PWS1.10 (-VOUT)
ADC1_NEG: LT113.1 (OUT_A), R3.1, R4.1, X1.1
GND: PWS1.1 (-VIN), PWS1.8 (COM), R2.2, R5.1, R7.2, X1.2, X1.3 (2), X1.4 (2), X1.5 (2), X2.2
INPUT1_NEG: LT113.3 (+IN_A), R8.1
V+: PWS1.16 (+VIN), X2.1

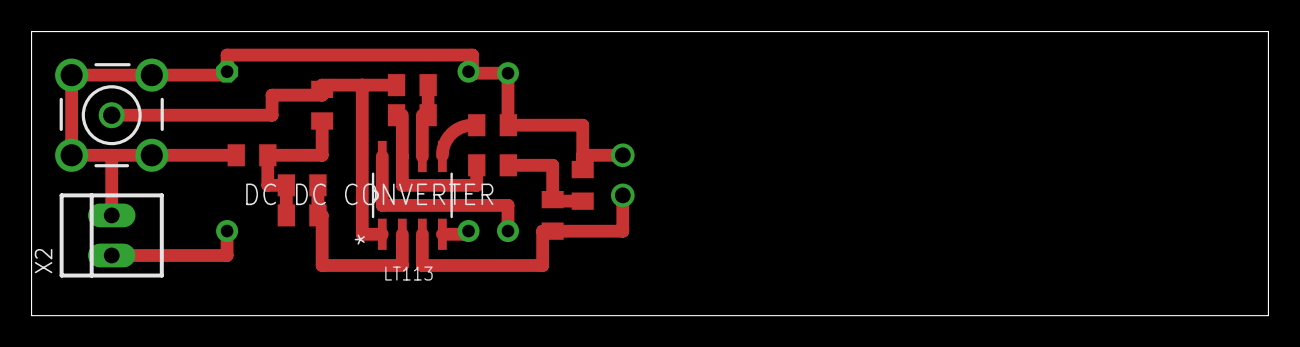
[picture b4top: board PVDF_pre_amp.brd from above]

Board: 2 copper layers, 78.4 x 18.0 mm, 14 parts (1 on the bottom side), 12 nets.

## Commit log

2023-03-08 Initial commit of work done in 2016.
2023-03-08 Added MIT LICENSE.txt
